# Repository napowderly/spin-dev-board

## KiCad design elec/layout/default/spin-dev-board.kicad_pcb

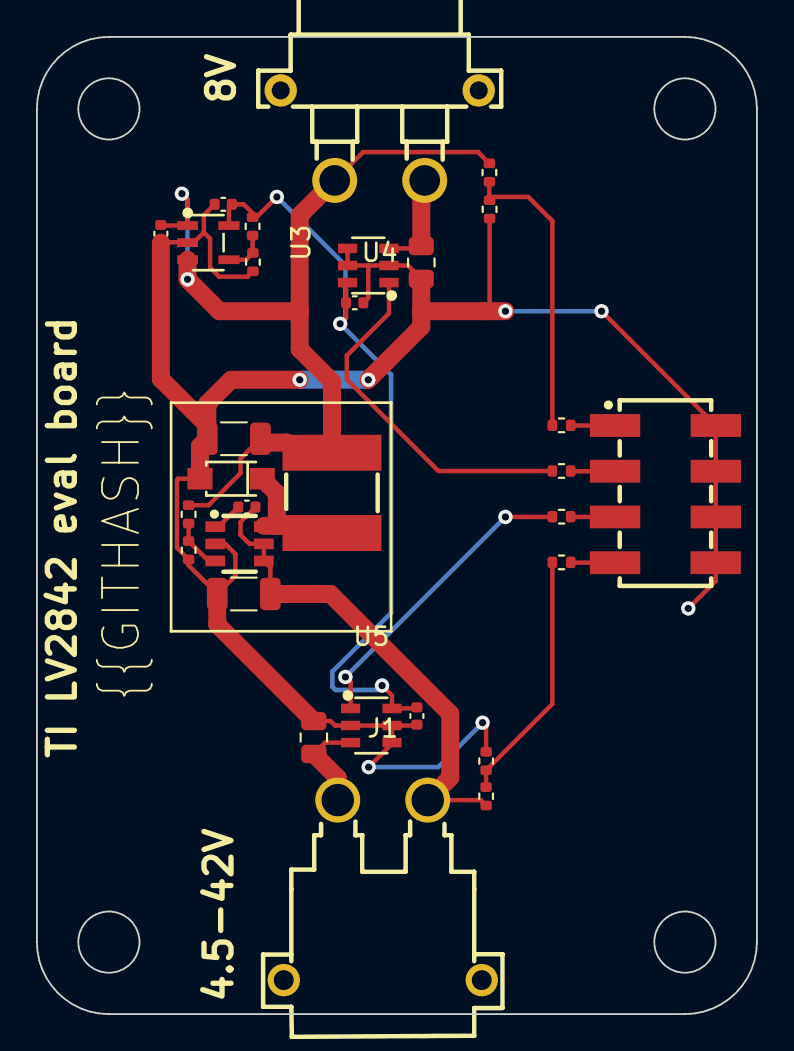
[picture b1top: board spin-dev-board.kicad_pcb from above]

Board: 2 copper layers, 40.0 x 54.3 mm, 30 parts (0 on the bottom side), 18 nets.

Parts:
C1, C2: Multilayer Ceramic Capacitors MLCC - SMD/SMT 4.7u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; C1206
C3: Multilayer Ceramic Capacitors MLCC - SMD/SMT 220n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; C0402
C4, C5: Multilayer Ceramic Capacitors MLCC - SMD/SMT 1uF 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; C0402
C6, C7: Multilayer Ceramic Capacitors MLCC - SMD/SMT 100n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; C0402
DS1: 40V 0.55V@2A 2A SOD-123F Schottky Barrier Diodes 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; ato-d7ff14dd-2a74-44cb-99b3-1745d3b17ea0
J1: CONN-TH_XT30PW-M
L1: 1A 47uH ±20% SMD Power Inductors ROHS; ato-2d2e488a-5f9f-46bd-846a-d9ea39a9e524
R1: Chip Resistor - Surface Mount 82KOhms ±5% 1/16W 0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; R0402
R2: Chip Resistor - Surface Mount 11KOhms ±5% 1/16W 0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; R0402
R3, R4, R5, R6: Chip Resistor - Surface Mount 1KOhms ±5% 1/16W 04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; R0402
R7: Chip Resistor - Surface Mount 18KOhms ±5% 1/16W 0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; R0402
R8, R12, R14: Chip Resistor - Surface Mount 10KOhms ±5% 1/16W 0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; R0402
R9, R10: Chip Resistor - Surface Mount 0.18Ohms ±5% 1/8W 0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; R0805
R11, R13: Chip Resistor - Surface Mount 20KOhms ±5% 1/16W 0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; R0402
U1: SOT-23-6_L2.9-W1.6-P0.95-LS2.8-BR
U2: HDR-SMD_8P-P2.54-V-M-R2-C4-LS7.4
U3: SOT-23-5_L3.0-W1.7-P0.95-LS2.8-BL
U4: CONN-TH_XT30PW-F-1
U5, U6: SOT-23-6_L2.9-W1.6-P0.95-LS2.8-TL

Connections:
SW: DS1.1, L1.1, U1.6
_1: R3.2, U2.1
_3: R4.2, U2.3
_5: R5.2, U2.5
_7: R6.2, U2.7
gnd: C1.2, C2.2, C4.2, C5.2, C6.2, C7.2, DS1.2, R2.2, R8.2, R9.2, R10.2, R12.2, R14.2, U1.2, U2.2, U2.4, U2.6, U2.8, U3.2, U5.2, U5.4, U5.5, U6.2, U6.4, U6.5
gnd-1: J1.1, R9.1, U5.3
gnd-2: R10.1, U4.1, U6.3
io: R1.2, R2.1, U1.3
io-1: R3.1, R13.2, R14.1
io-2: R4.1, U6.1
io-3: R5.1, U5.1
io-4: R6.1, R11.2, R12.1
io-5: R7.2, R8.1, U3.4
vcc: C1.1, C3.2, J1.2, R11.1, U1.4, U1.5
vcc-1: C2.1, C4.1, L1.2, R1.1, R13.1, U3.1, U3.3, U4.2
vcc-2: C3.1, U1.1
vcc-3: C5.1, C6.1, C7.1, R7.1, U3.5, U5.6, U6.6

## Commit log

2024-02-04 Configure project
2024-02-05 building
2024-02-05 layout complete
2024-02-05 deleting unused layouts
2024-02-05 adding dependencies
2024-02-05 fixing deps
2024-02-05 fixing generics version
2024-02-05 fixing tag
2024-02-05 cleanup silk screen
2024-02-05 drc fixes
